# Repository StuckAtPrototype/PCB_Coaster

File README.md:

# PCB Coaster - StuckAtPrototype

## Youtube Video
A bit of a back-story of how this project came to be. 

Sub if you like what you see.

*Some pictures of the project*

## Project Structure
The project consists of
1. Firmware
2. Hardware
3. Mechanical

These are structured into their own files. I could have used submodules, but decided against it.  

### 1. Firmware
Code for the coaster. This lives on the ESP32

#### Requirements
- ESP32 IDF version 5.4
- Target set to ESP32-H2
- Install managed components  

##### Required Managed Components
1. lvgl 
2. espressif esp lvgl port

### 2. Hardware

#### Schematic
PDF schematic included for your viewing pleasure. File `PCB_Coaster_v0.2_Schematic.pdf`

#### PCBs
All the gerber files you'd need to send to a fab house. File `PCB coaster v0.2.zip`

#### BOM
Bill of materials file `coaster-BOM-v0.2.csv`

#### Kicad
All the files you'd need to expand and work on this further. If you'd like.

### 3. Mechanical

#### Diffuser
`PCB Coaster diffuser.step`
You can print this part with clear ABS fillament for best results. 

#### Screen Holder
`PCB Coaster screen holder.step`
I printed this part with an SLA printer, it can probably do ok with a filament printer too 

#### Spacers
`PCB Coaster spacer.step`
These print best on SLA. Filament printer will not achieve flat tops, though it might work. Best printed with SLA.  

#### Screen protector
I used a Cricut machine and a thin accental plastic to cut out the screen protector. Ideally, this would be made of tempered glass. (maybe one day)

## If you take it further
Let me know if you ever make one of these, I'd love to see it. Seriously, that'd be exciting and inspiring to keep making my projects open source!

## And if you got this far...
Consider signing up for my mailing list. As I run into problems when making these projects, I fire off an email with a small write up explaing the problem and the solution I found. Here is the link https://landing.stuckatprototype.com/exclusive

Stay fun, StuckAtPrototype

---
## License
### Apache 2.0 -- i.e. use as you'd like
http://www.apache.org/licenses/LICENSE-2.0

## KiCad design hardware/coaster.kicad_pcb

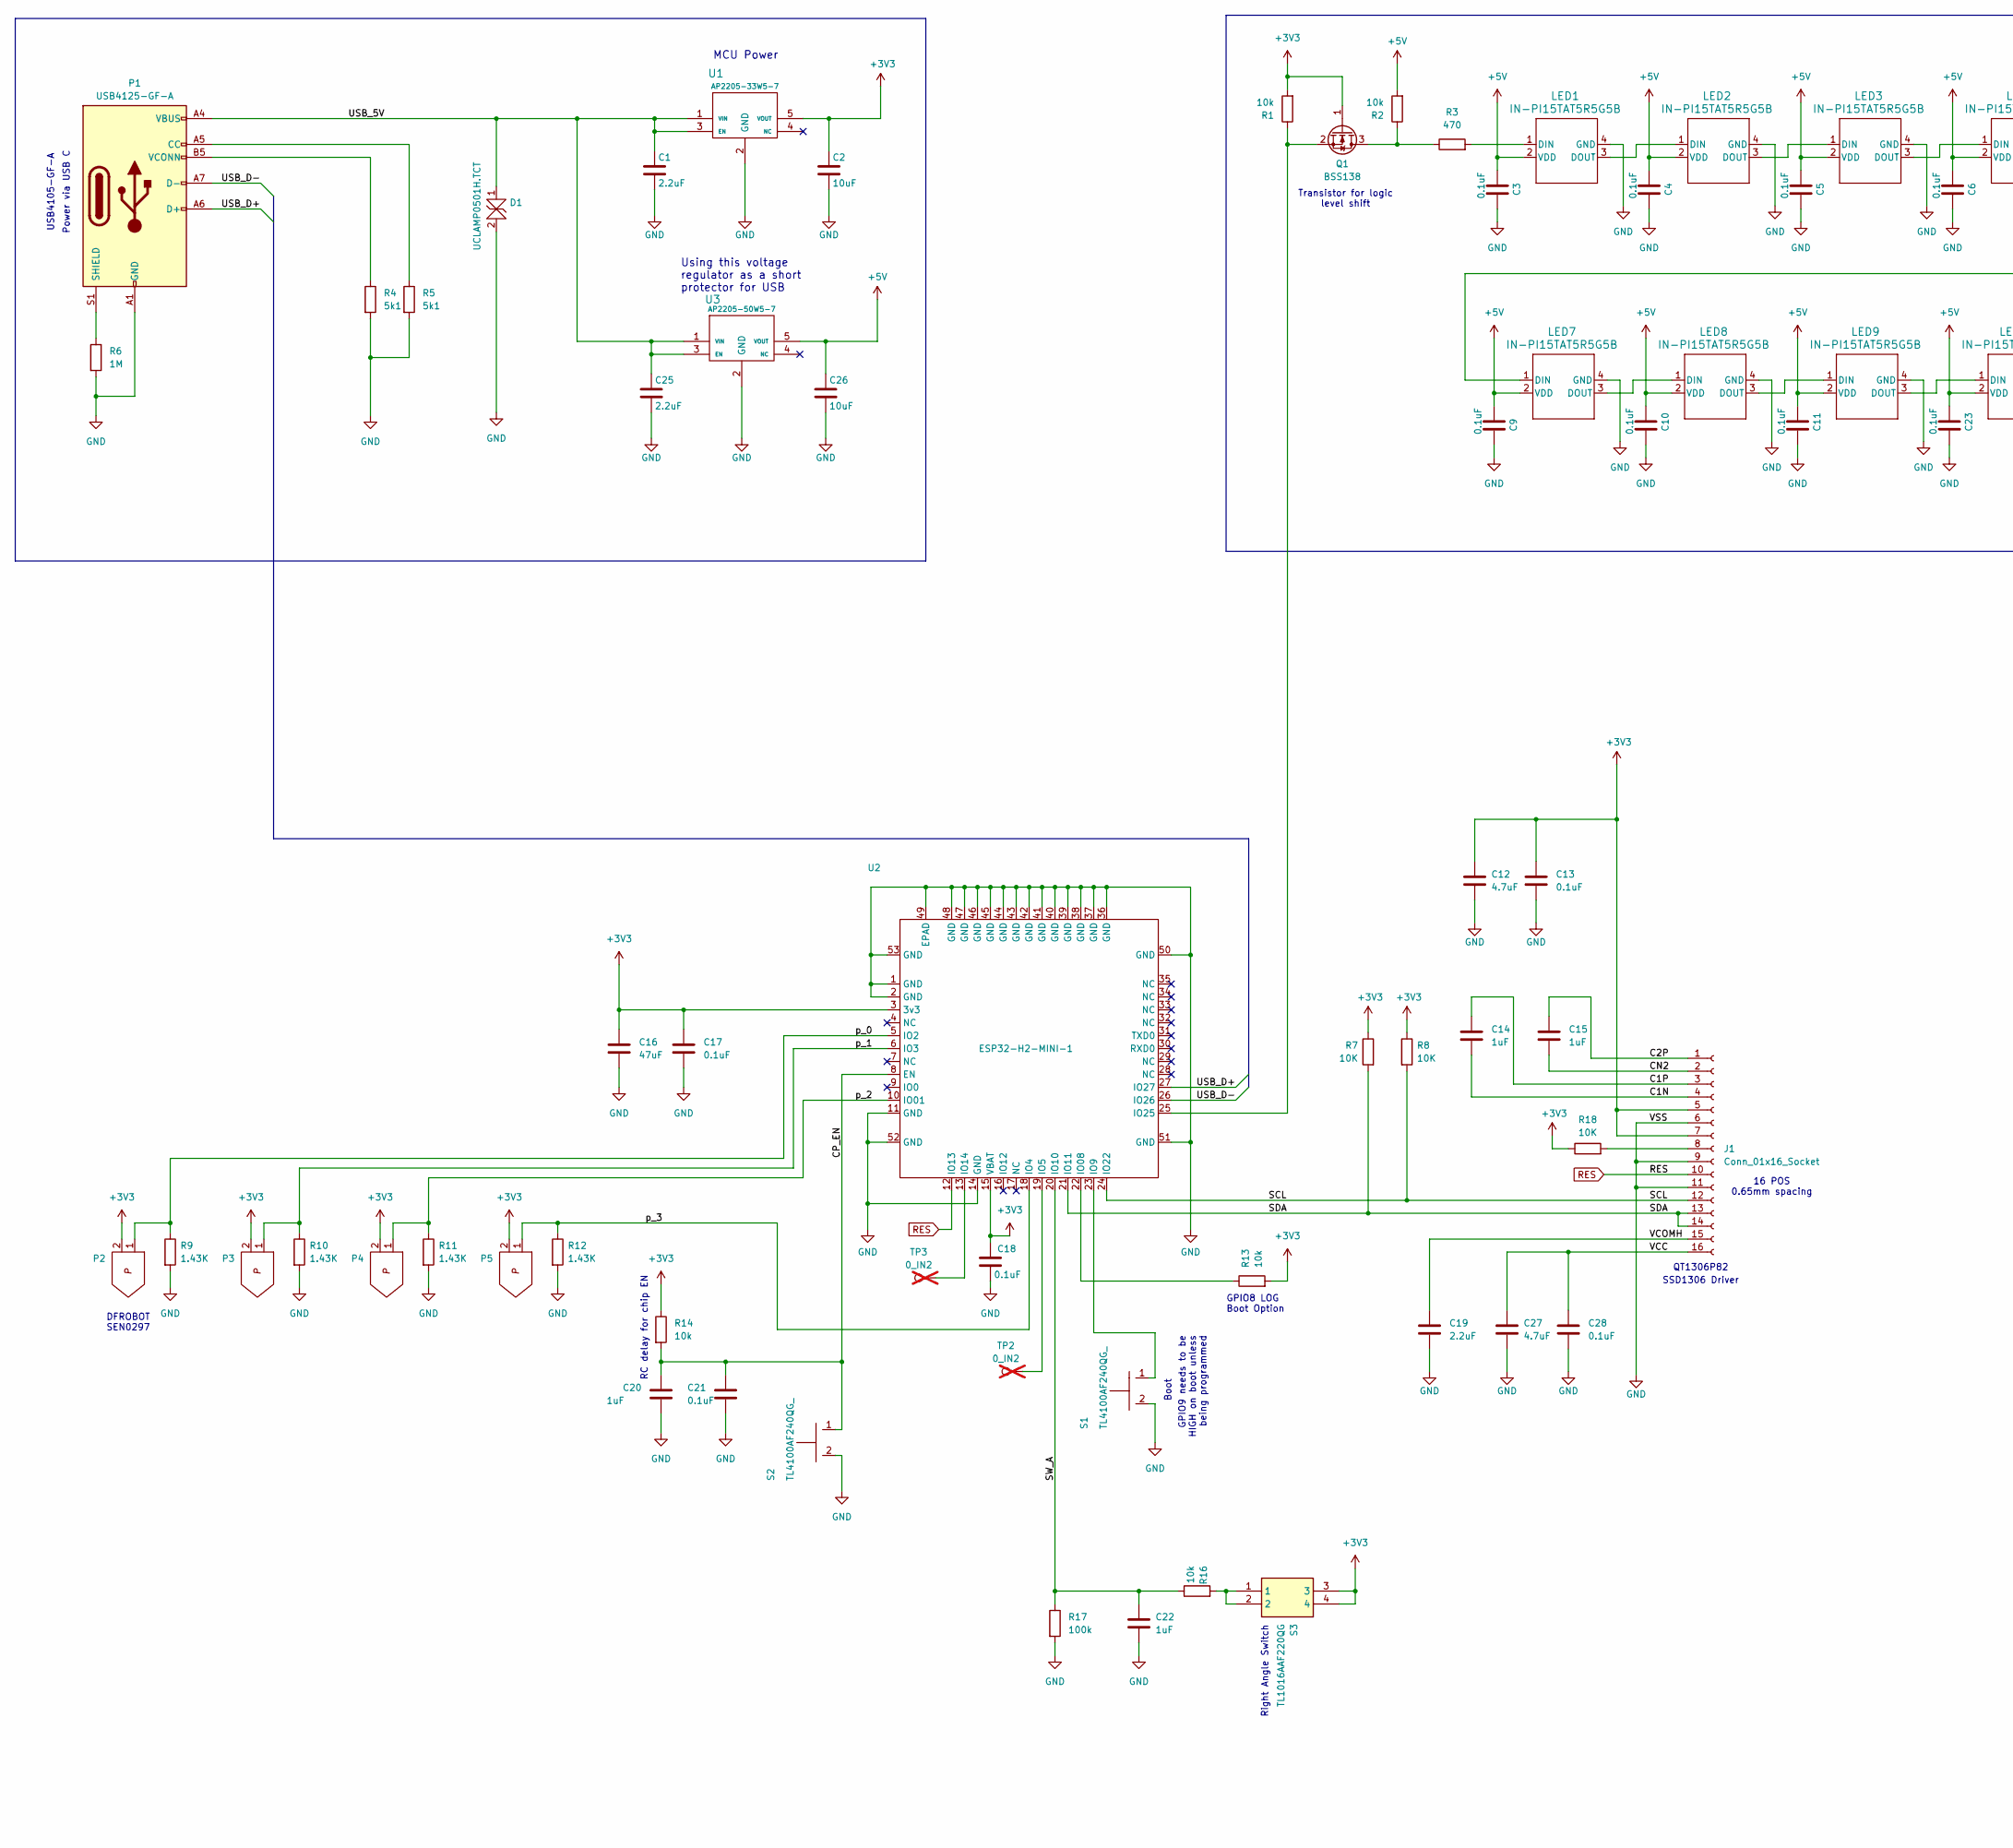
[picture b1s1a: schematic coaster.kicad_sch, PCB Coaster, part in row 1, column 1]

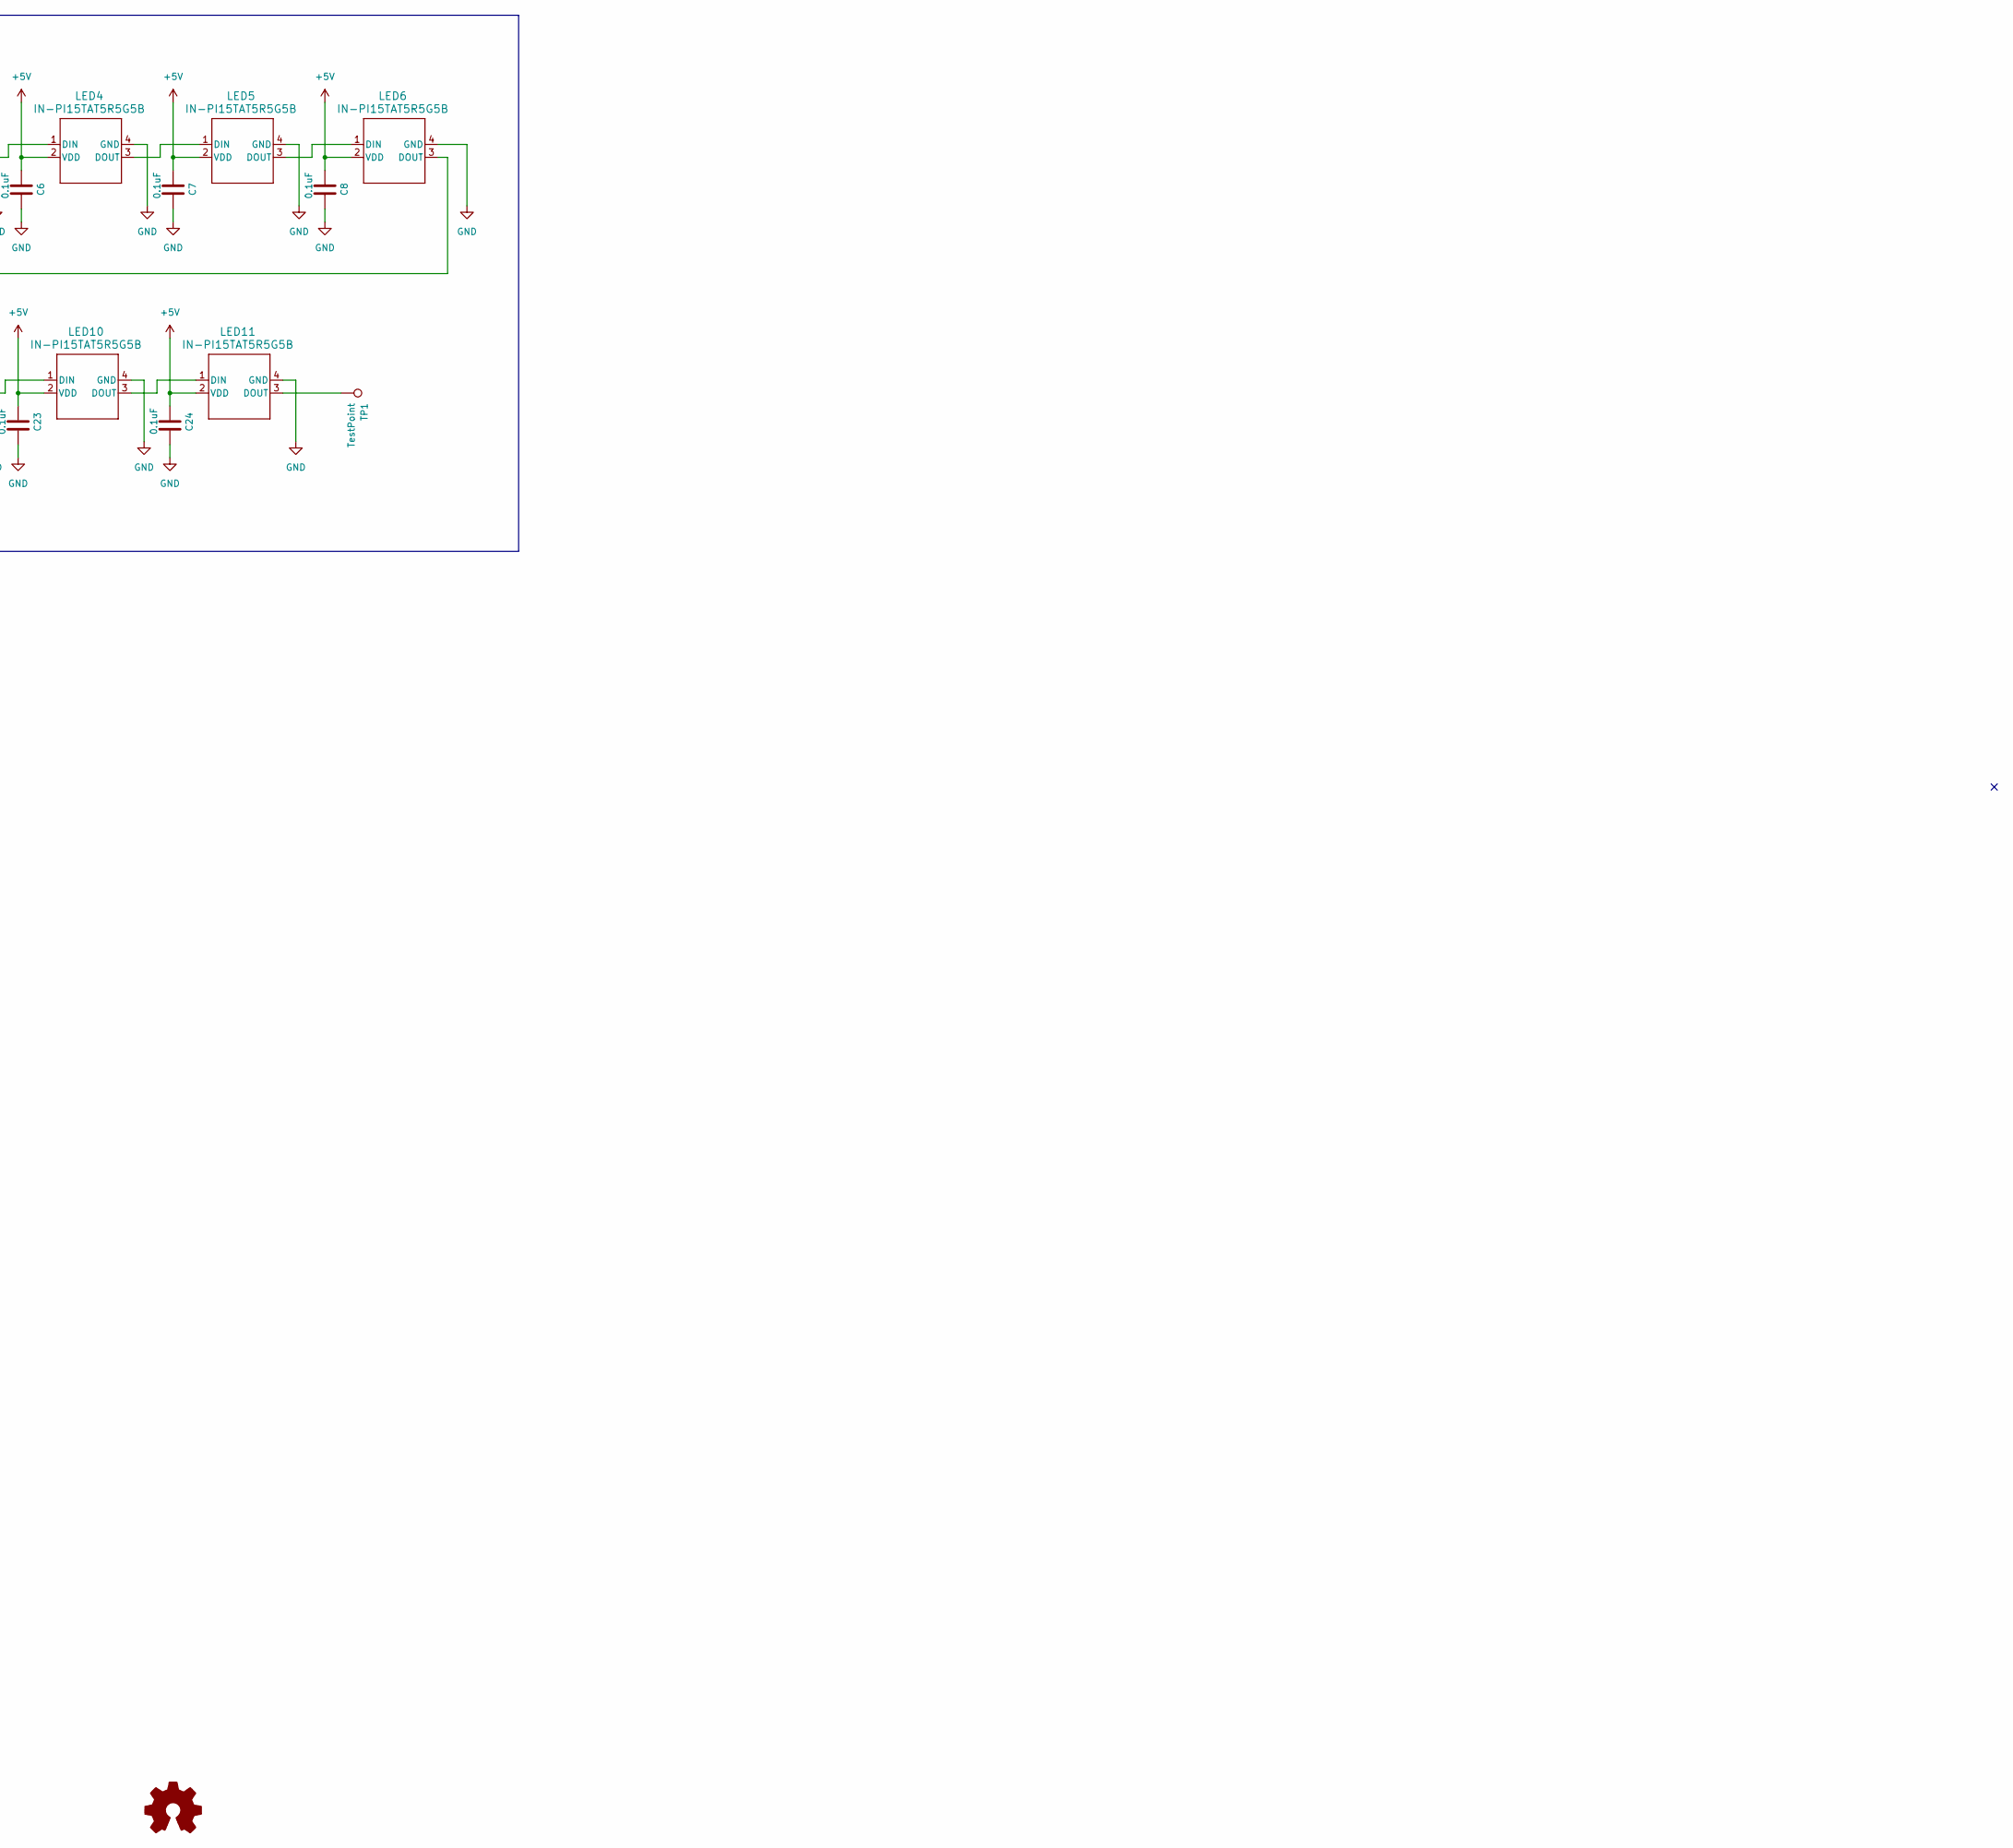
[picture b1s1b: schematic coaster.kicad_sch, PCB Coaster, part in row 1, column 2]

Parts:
C1, C19, C25: 2.2uF; C_0603_1608Metric
C2, C26: 10uF; C_0603_1608Metric
C3, C4, C5, C6, C7, C8, C9, C10, C11, C13, C17, C18, C21, C23, C24, C28: 0.1uF; C_0603_1608Metric
C12, C27: 4.7uF; C_0603_1608Metric
C14, C15, C20, C22: 1uF; C_0603_1608Metric
C16: 47uF; C_0603_1608Metric
D1: UCLAMP0501H.TCT; D_SOD-523
J1: Conn_01x16_Socket; SMT_FFC_16X0.65
LED1, LED2, LED3, LED4, LED5, LED6, LED7, LED8, LED9, LED10, LED11: IN-PI15TAT5R5G5B; IN-PI15_INL
P1: USB4125-GF-A; GCT_USB4105-GF-A
P2, P3, P4, P5: SEN0297
Q1: BSS138; SOT-23
R1, R2, R13, R14, R16: 10k; R_0603_1608Metric
R3: 470; R_0603_1608Metric
R4, R5: 5k1; R_0603_1608Metric
R6: 1M; R_0603_1608Metric
R7, R8, R18: 10K; R_0603_1608Metric
R9, R10, R11, R12: 1.43K; R_0603_1608Metric
R17: 100k; R_0603_1608Metric
S1, S2: TL4100AF240QG_; SW_PTS810_SJM_250_SMTR_LFS
S3: TL1016AAF220QG; Mouser Part Number 612-TL1016AAF220QG
TP1: TestPoint; TestPoint_Pad_2.0x2.0mm
TP2, TP3: 0_IN2; TestPoint_Pad_1.0x1.0mm; not fitted
U1: AP2205-33W5-7; AP2204
U2: ESP32-H2-MINI-1; MODULE_ESP32-H2-MINI-1-H2
U3: AP2205-50W5-7; AP2204

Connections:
+3V3: C2.1, C12.1, C13.1, C16.1, C17.1, C18.1, J1.5, J1.7, P2.2, P3.2, P4.2, P5.2, Q1.1 (G), R1.2, R7.1, R8.1, R13.2, R14.1, R18.1, S3.3, S3.4, U1.5 (VOUT), U2.3 (3v3), U2.15 (VBAT)
+5V: C3.1, C4.1, C5.1, C6.1, C7.1, C8.1, C9.1, C10.1, C11.1, C23.1, C24.1, C26.1, LED1.2 (VDD), LED2.2 (VDD), LED3.2 (VDD), LED4.2 (VDD), LED5.2 (VDD), LED6.2 (VDD), LED7.2 (VDD), LED8.2 (VDD), LED9.2 (VDD), LED10.2 (VDD), LED11.2 (VDD), R2.2, U3.5 (VOUT)
/C1N: C14.2, J1.4
/C1P: C14.1, J1.3
/C2P: C15.1, J1.1
/CN2: C15.2, J1.2
/CP_EN: C20.1, C21.1, R14.2, S2.1, U2.8 (EN)
/SCL: J1.12, R8.2, U2.24 (IO22)
/SDA: J1.13, J1.14, R7.2, U2.21 (IO11)
/SW_A: C22.1, R16.1, R17.1, U2.20 (IO10)
/USB_5V: C1.1, C25.1, D1.1, P1.A4 (VBUS), P1.A9 (VBUS), P1.B4 (VBUS), P1.B9 (VBUS), U1.1 (VIN), U1.3 (EN), U3.1 (VIN), U3.3 (EN)
/USB_D+: P1.A6 (D+), U2.27 (IO27)
/USB_D-: P1.A7 (D-), U2.26 (IO26)
/VCC: C27.1, C28.1, J1.16
/VCOMH: C19.1, J1.15
/p_0: P2.1, R9.1, U2.5 (IO2)
/p_1: P3.1, R10.1, U2.6 (IO3)
/p_2: P4.1, R11.1, U2.10 (IO01)
/p_3: P5.1, R12.1, U2.18 (IO4)
GND: C1.2, C2.2, C3.2, C4.2, C5.2, C6.2, C7.2, C8.2, C9.2, C10.2, C11.2, C12.2, C13.2, C16.2, C17.2, C18.2, C19.2, C20.2, C21.2, C22.2, C23.2, C24.2, C25.2, C26.2, C27.2, C28.2, D1.2, J1.6, J1.9, J1.11, LED1.4 (GND), LED2.4 (GND), LED3.4 (GND), LED4.4 (GND), LED5.4 (GND), LED6.4 (GND), LED7.4 (GND), LED8.4 (GND), LED9.4 (GND), LED10.4 (GND), LED11.4 (GND), P1.A1 (GND), P1.A12 (GND), P1.B1 (GND), P1.B12 (GND), R4.2, R5.2, R6.2, R9.2, R10.2, R11.2, R12.2, R17.2, S1.2, S2.2, U1.2 (GND), U2.1 (GND), U2.2 (GND), U2.11 (GND), U2.14 (GND), U2.36 (GND), U2.37 (GND), U2.38 (GND), U2.39 (GND), U2.40 (GND), U2.41 (GND), U2.42 (GND), U2.43 (GND), U2.44 (GND), U2.45 (GND), U2.46 (GND), U2.47 (GND), U2.48 (GND), U2.49 (EPAD), U2.50 (GND), U2.51 (GND), U2.52 (GND), U2.53 (GND), U3.2 (GND)
unnamed: J1.8, R18.2
unnamed: LED1.1 (DIN), R3.2
unnamed: LED1.3 (DOUT), LED2.1 (DIN)
unnamed: LED2.3 (DOUT), LED3.1 (DIN)
unnamed: LED3.3 (DOUT), LED4.1 (DIN)
unnamed: LED4.3 (DOUT), LED5.1 (DIN)
unnamed: LED5.3 (DOUT), LED6.1 (DIN)
unnamed: LED6.3 (DOUT), LED7.1 (DIN)
unnamed: LED7.3 (DOUT), LED8.1 (DIN)
unnamed: LED8.3 (DOUT), LED9.1 (DIN)
unnamed: LED9.3 (DOUT), LED10.1 (DIN)
unnamed: LED10.3 (DOUT), LED11.1 (DIN)
unnamed: LED11.3 (DOUT), TP1.1
unnamed: P1.A5 (CC), R5.1
unnamed: P1.S1 (SHIELD), R6.1
unnamed: P1.B5 (VCONN), R4.1
unnamed: Q1.3 (D), R2.1, R3.1
unnamed: Q1.2 (S), R1.1, U2.25 (IO25)
unnamed: R16.2, S3.1, S3.2
unnamed: TP2.1, U2.19 (IO5)
unnamed: R13.1, U2.22 (IO08)
unnamed: S1.1, U2.23 (IO9)
unnamed: TP3.1, U2.13 (IO14)
RES: J1.10, U2.12 (IO13)

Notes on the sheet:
MCU Power
16 POS 0.65mm spacing
Power via USB C
RC delay for chip EN
Using this voltage regulator as a short protector for USB
GPIO8 LOG Boot Option
Boot
Right Angle Switch
GPIO9 needs to be HIGH on boot unless being programmed
USB4105-GF-A
Transistor for logic level shift
SSD1306 Driver
DFROBOT SEN0297
QT1306P82

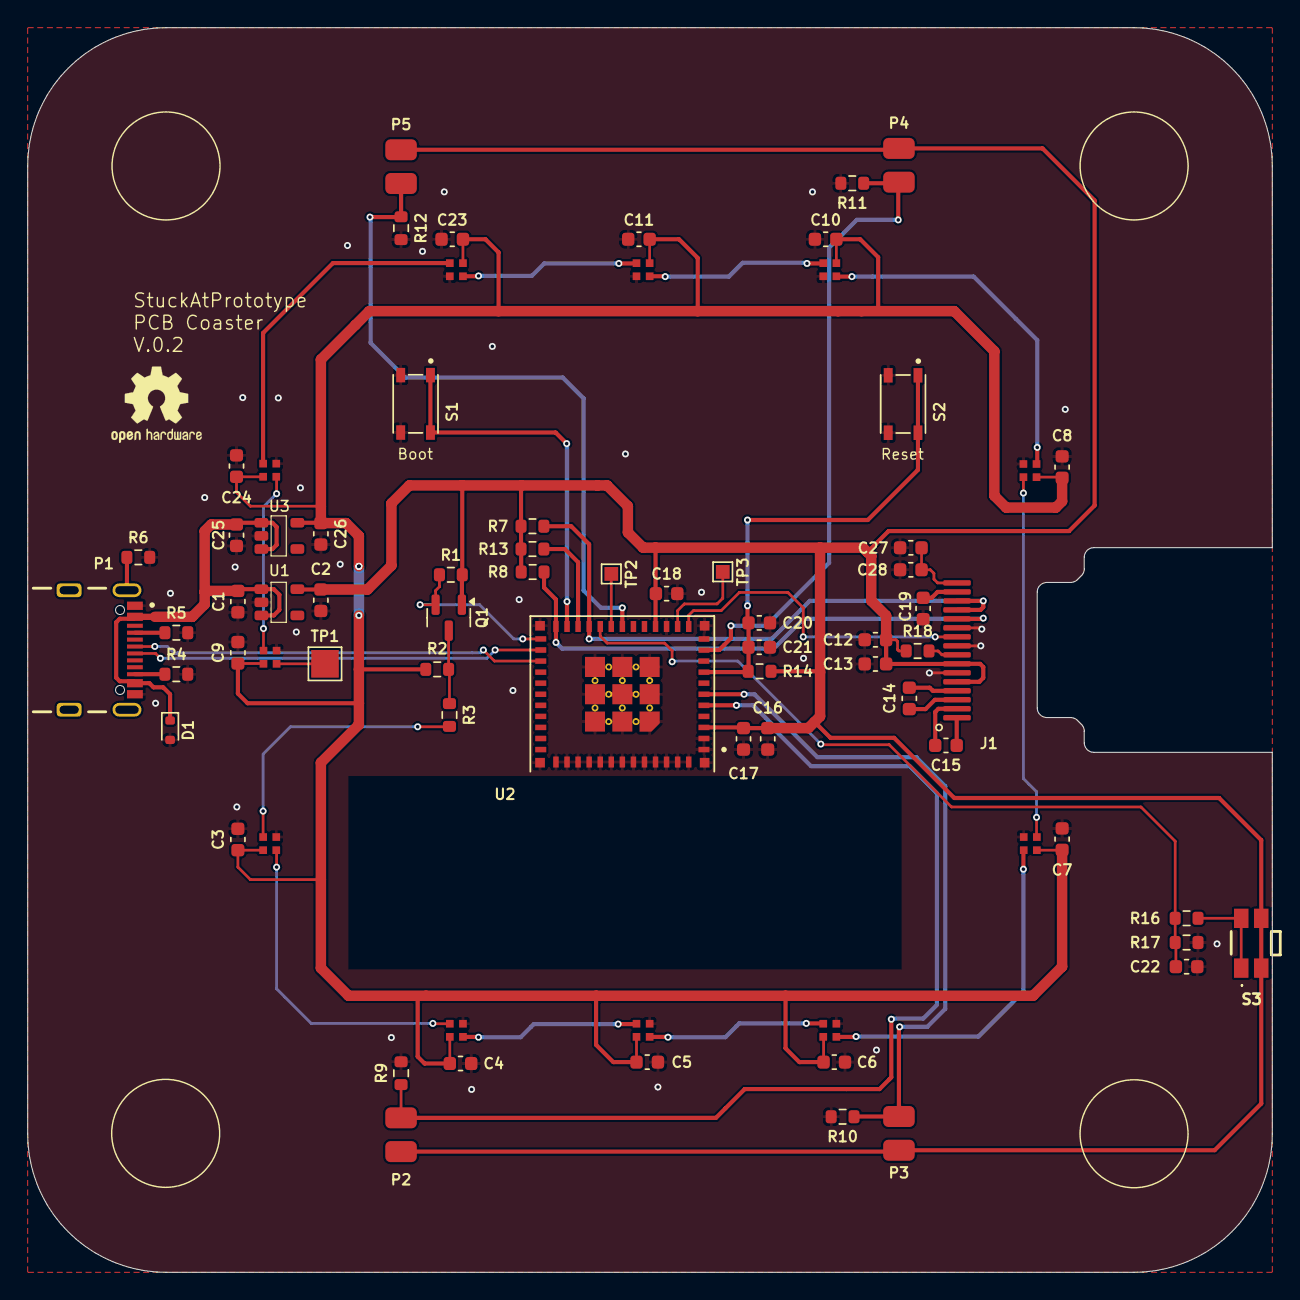
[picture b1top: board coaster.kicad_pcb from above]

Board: 2 copper layers, 90.0 x 90.0 mm, 73 parts (0 on the bottom side), 44 nets.

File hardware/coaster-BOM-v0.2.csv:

Id,Designator,Footprint,Quantity,Designation,Supplier and ref,,PnP,
1,R17,R_0603_1608Metric,1,100k,,,y,
2,"R5,R4",R_0603_1608Metric,2,5k1,,,y,
3,U3,AP2204,1,AP2205,AP2205-33W5-7,3v3,,
4,U1,AP2204,1,AP2205,AP2205-50W5-7,5v,,bought
5,"C18,C4,C28,C10,C11,C17,C5,C3,C23,C6,C24,C8,C13,C7,C9,C21",C_0603_1608Metric,16,0.1uF,,,y,
6,"LED9,LED6,LED1,LED8,LED7,LED3,LED11,LED4,LED5,LED10,LED2",IN-PI15_INL,11,IN-PI15TAT5R5G5B,IN-PI15TAT5R5G5B,,,bought
7,"R11,R9,R10,R12",R_0603_1608Metric,4,1.43K,,,y,
8,R3,R_0603_1608Metric,1,470,,,,bought
9,"C25,C19,C1",C_0603_1608Metric,3,2.2uF,,,,bought
10,"R14,R13,R1,R2,R16",R_0603_1608Metric,5,10k,,,y,
11,P1,GCT_USB4105-GF-A,1,USB_C_Plug_USB2.0,USB4125-GF-A,,,bought
12,"C12,C27",C_0603_1608Metric,2,4.7uF,,,y,
13,"C26,C2",C_0603_1608Metric,2,10uF,,,y,
14,D1,D_SOD-523,1,TPD1E10B06DPYR,UCLAMP0501H.TCT,*Changed ,,bought
15,Q1,SOT-23,1,BSS138,BSS138,,,bought
16,"R8,R18,R7",R_0603_1608Metric,3,10K,,,y,
17,"P3,P2,P5,P4",SEN0297,4,SEN0297,SEN0297,,,
18,U2,MODULE_ESP32-H2-MINI-1-H2,1,ESP32-H2-MINI-1,ESP32-H2-MINI-1,,,
19,"C14,C15,C20,C22",C_0603_1608Metric,2,1uF,,,y,
20,C16,C_0603_1608Metric,1,47uF,,,,
21,R6,R_0603_1608Metric,1,1M,,,y,
22,S3,TL1016AAF220QG,1,TL1016AAF220QG,TL1016AAF220QG,,,bought

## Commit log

2025-03-08 firmware version 1.0
2025-03-08 adding readme
2025-03-08 hardware version 0.2
2025-03-08 mechanicals
2025-03-08 project pictures
2025-03-08 gitignore
